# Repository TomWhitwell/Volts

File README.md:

##Turing Mini Voltages Expander   

This is a simple, low-parts count, low-current expander for the Turing Machine Random Sequencer in 4HP. 

It acts like a variable 5-bit digital-to-analog converter, taking 5 bits from the Turing Machine GATES expansion port, running them through five potentiometers and giving one summed voltage output.   

Multiple mini expanders can be daisychained from one Turing sequencer to give melodically different outputs that are all related to (and change with) the main Turing sequence.   

Designed in one day while on holiday in Cornwall.   

NB: the panel design in this repository is a bit strange; raw fibreglass with gold lines and no text - you might want to tweak it if you want a panel that matches the other the Turing expanders. 

BOM: 
- 5 x Vertical 50k Linear Potentiometers ([Alpha 9mm](https://www.thonk.co.uk/shop/alpha-9mm-pots/) will work well)
- 8 x 10k Resistors 
- 1 x 1k Resistor 
- 1 x TL072 Op Amp 
- 2 x 100n Ceramic Capacitors 
- 1 x [Thonkiconn Socket](https://www.thonk.co.uk/shop/thonkiconn-3-5mm-jack-sockets-x50/)  
- 2 x 16 Pin Headers 2x8 (for example 649-67997-216HLF from Mouser)
- 1 x Ribbon cable
- 5 x Knobs

This board should be built with pots that bolt to the panel, like the Alphas above. Plastic shaft pots (or the little ones with an indicator line on the shaft) will work fine, but the only support between the board and the panel will be the nut on the socket. There is a mounting hole on the PCB, so you can screw an 11m hex spacer to that, and epoxy the other end to the panel, if you want to use those pots. 

Status:  
January 2016: Updated prototype built, working well. 
September 2015: First board validated idea, contained embarrassing errors. Those fixed, second prototypes ordered.  
August 2015: Awaiting first prototypes

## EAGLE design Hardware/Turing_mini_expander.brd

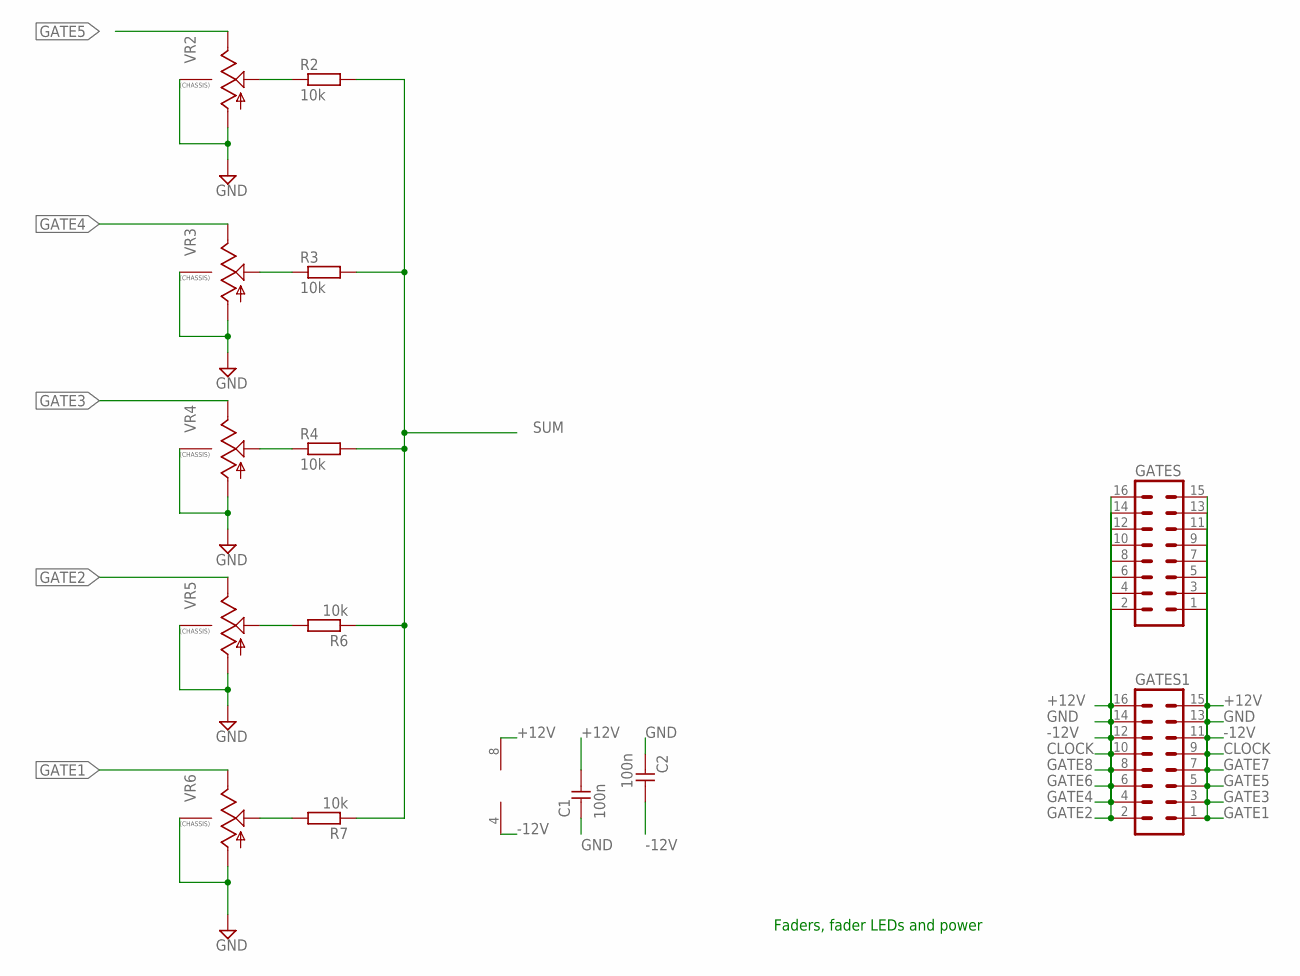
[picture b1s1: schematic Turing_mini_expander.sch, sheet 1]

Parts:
C1, C2: 100n; C050-024X044
GATES, GATES1: MA08-2
R2, R3, R4, R6, R7: 10k; 7MM_RESISTOR
U1: TL072_; DIL08
VR2, VR3, VR4, VR5, VR6: 9MM_SNAP-IN_POT_CHASSIS; 9MM_SNAP-IN_POT

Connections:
+12V: C1.1, GATES.15, GATES.16, GATES1.15, GATES1.16, U1.8 (V+)
-12V: C2.1, GATES.11, GATES.12, GATES1.11, GATES1.12, U1.4 (V-)
CLOCK: GATES.9, GATES.10, GATES1.9, GATES1.10
GATE1: GATES.1, GATES1.1, VR6.3 (E)
GATE2: GATES.2, GATES1.2, VR5.3 (E)
GATE3: GATES.3, GATES1.3, VR4.3 (E)
GATE4: GATES.4, GATES1.4, VR3.3 (E)
GATE5: GATES.5, GATES1.5, VR2.3 (E)
GATE6: GATES.6, GATES1.6
GATE7: GATES.7, GATES1.7
GATE8: GATES.8, GATES1.8
GND: C1.2, C2.2, GATES.13, GATES.14, GATES1.13, GATES1.14, VR2.1 (A), VR2.CHASSIS2, VR3.1 (A), VR3.CHASSIS2, VR4.1 (A), VR4.CHASSIS2, VR5.1 (A), VR5.CHASSIS2, VR6.1 (A), VR6.CHASSIS2; also elsewhere on the board
unnamed: R2.1, VR2.2 (S)
unnamed: R3.1, VR3.2 (S)
unnamed: R4.1, VR4.2 (S)
unnamed: R6.2, VR5.2 (S)
unnamed: R7.2, VR6.2 (S)
SUM: R2.2, R3.2, R4.2, R6.1, R7.1; also elsewhere on the board

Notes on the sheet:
Faders, fader LEDs and power

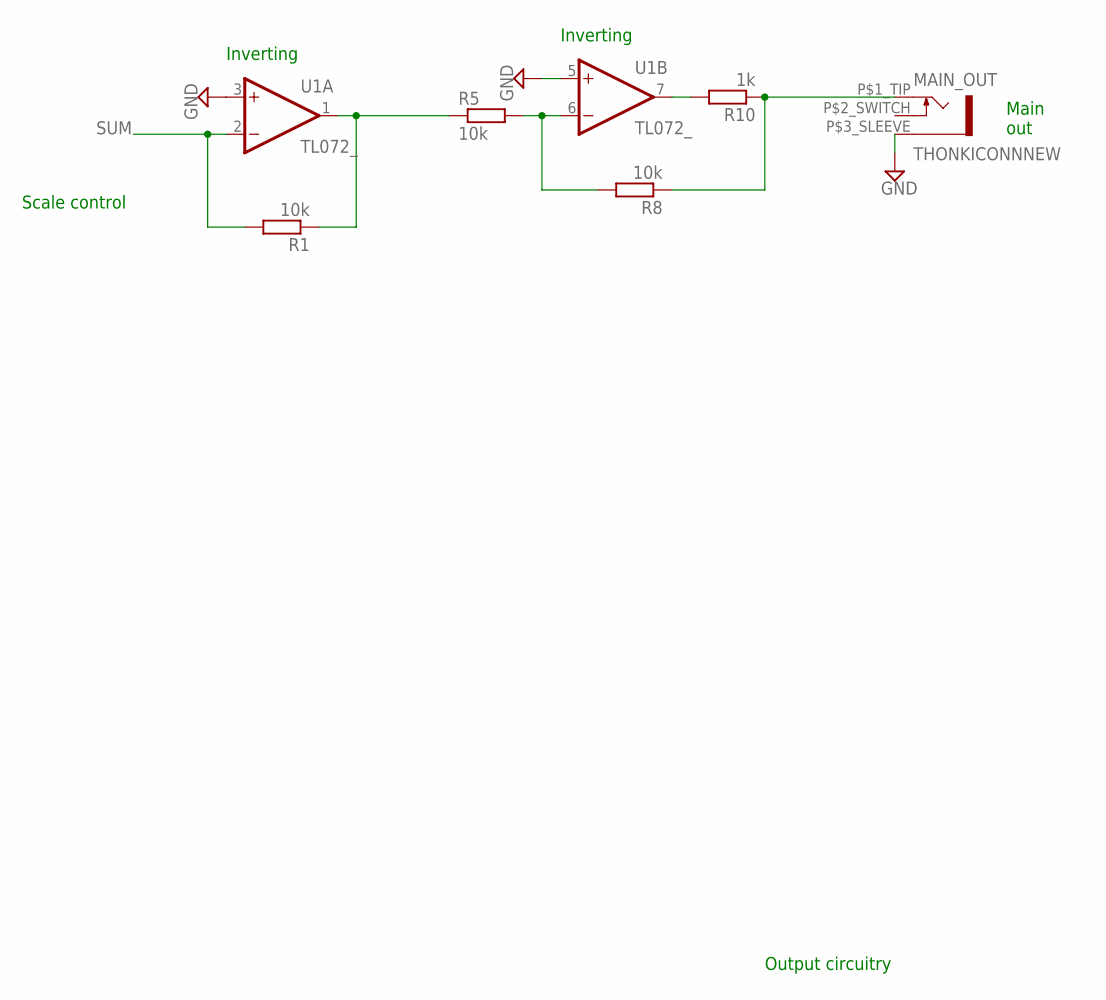
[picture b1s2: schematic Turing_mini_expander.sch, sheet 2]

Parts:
MAIN_OUT: THONKICONNNEW; WQP-PJ301M-12_JACK
R1, R5, R8: 10k; 7MM_RESISTOR
R10: 1k; 7MM_RESISTOR
U1: TL072_; DIL08

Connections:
GND: MAIN_OUT.P$3_SLEEVE (SLEEVE), U1.3 (+IN), U1.5 (+IN); also elsewhere on the board
unnamed: R5.2, R8.2, U1.6 (-IN)
unnamed: MAIN_OUT.P$1_TIP (TIP), R8.1, R10.1
unnamed: R10.2, U1.7 (OUT)
unnamed: R1.1, R5.1, U1.1 (OUT)
SUM: R1.2, U1.2 (-IN); also elsewhere on the board

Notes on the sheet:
Scale control
Main out
Output circuitry
Inverting

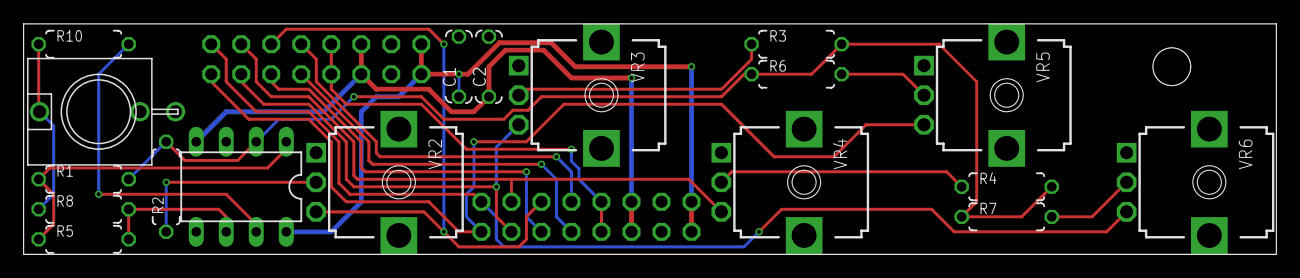
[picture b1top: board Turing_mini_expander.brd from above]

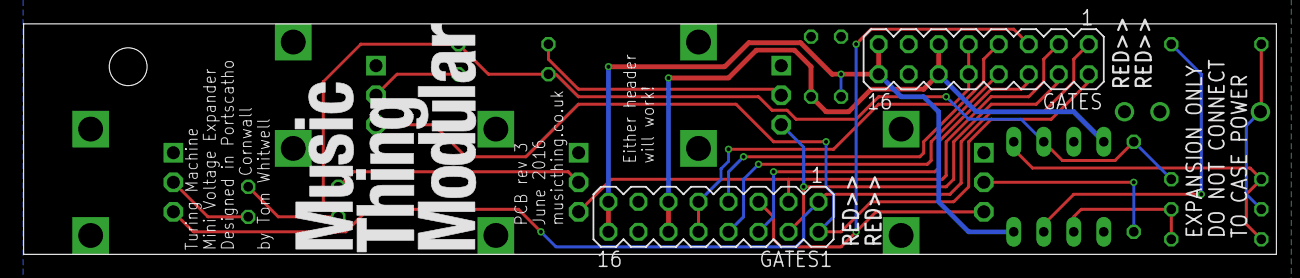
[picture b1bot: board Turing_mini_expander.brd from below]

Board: 4 copper layers, 106.0 x 19.5 mm, 21 parts (2 on the bottom side), 22 nets.

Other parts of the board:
U$1: MOUNTING_HOLE

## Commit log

2015-08-26 Initial upload
2015-09-06 Thonkiconn error corrected and re-routed
2015-09-06 Fixes after first photo
    Fixes #2, fixes #3, fixes #4
2015-09-06 Centre pcb on panel
    fixes #1
2015-09-12 Add vector logo to back of board
2015-09-12 vector logos on panel
2015-09-12 reroute fatter traces
2015-09-12 Rev 2 Board and Panel complete and prototypes ordered
2015-09-12 tidy up
2015-10-19 Merge remote-tracking branch 'origin/master'
    Conflicts:
    Hardware/Eagle/Turing_mini_expander.brd
2016-01-05 Revert "Merge remote-tracking branch 'origin/master'"
    This reverts commit c677e9c759e717a54841b66673ad6128330ede4f.
2016-01-05 Value changes
2016-01-24 Folder reorganisation
2016-05-26 Upload panel artwork
2016-06-09 Rev 3 PCB
    Reverses order of pots
2017-11-05 Add schematic
2017-11-05 Both pages in schematic now!
